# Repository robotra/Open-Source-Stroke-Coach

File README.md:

# Open-Source-Stroke-Coach
This project aims to replicate some of the funcationality of the NK StrokeCoach, but at a much lower cost. 

Current hardware requirement: 
* ESP32 DOIT dev kit
* mpu6050 accelerometer
* I2C display

## Software
Stroke detection is based on the values from the accelerometer, smoothed by a low pass filter. This filtered data is then used to feed a peak detection algorithm, and time between peaks is used to calculate stroke rate. 

## To-do
* GPS
* Save to SD card as GPX file
* Then build out integration to the Strava API
* BLE HRM connection
* UI
* Minimize scope creep
* PCB

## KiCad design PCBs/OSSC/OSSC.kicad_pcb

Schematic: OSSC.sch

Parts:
C1, C3, C5: 0.1uF; C_0402_1005Metric
C2: 2.2nF; C_0402_1005Metric
C4: 2.3nF; C_0402_1005Metric
J1: Conn_01x02_Female; JST_SH_SM02B-SRSS-TB_1x02-1MP_P1.00mm_Horizontal
J2: Conn_01x04; PinHeader_1x04_P1.27mm_Vertical
J3, J4: Conn_01x01; PinHeader_1x01_P1.00mm_Vertical
R1: 10k; R_0603_1608Metric_Pad1.05x0.95mm_HandSolder
R2, R3: 10k; R_0402_1005Metric
U1: MCP1700-3302E_SOT23; SOT-23
U2: ESP32-WROOM-32
U3: MPU-6050; InvenSense_QFN-24_4x4mm_P0.5mm

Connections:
+BATT: J1.2, U1.3 (VI)
GND: C1.1, C3.2, C4.2, C5.1, J1.1, J2.2, U1.1 (GND), U2.1 (GND), U2.15 (GND), U2.38 (GND), U2.39 (GND), U3.1 (CLKIN), U3.9 (AD0), U3.11 (FSYNC), U3.18 (GND)
I2C-SCL: J2.3, R3.2, U2.36 (IO22), U3.23 (SCL)
I2C-SDA: J2.4, R2.2, U2.33 (IO21), U3.24 (SDA)
MPU-6050-INT: U2.23 (IO15), U3.12 (INT)
unnamed: C1.2, R1.1, U2.3 (EN)
unnamed: C2.1, U3.8 (VDDIO)
unnamed: C4.1, U3.20 (CPOUT)
unnamed: C5.2, U3.10 (REGOUT)
unnamed: J3.1, U2.35 (TXD0/IO1)
unnamed: J4.1, U2.34 (RXD0/IO3)
VCC-3.3V: C2.2, C3.1, J2.1, R1.2, R2.1, R3.1, U1.2 (VO), U2.2 (VDD), U3.13 (VDD)

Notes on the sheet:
I2C-Connector for Display

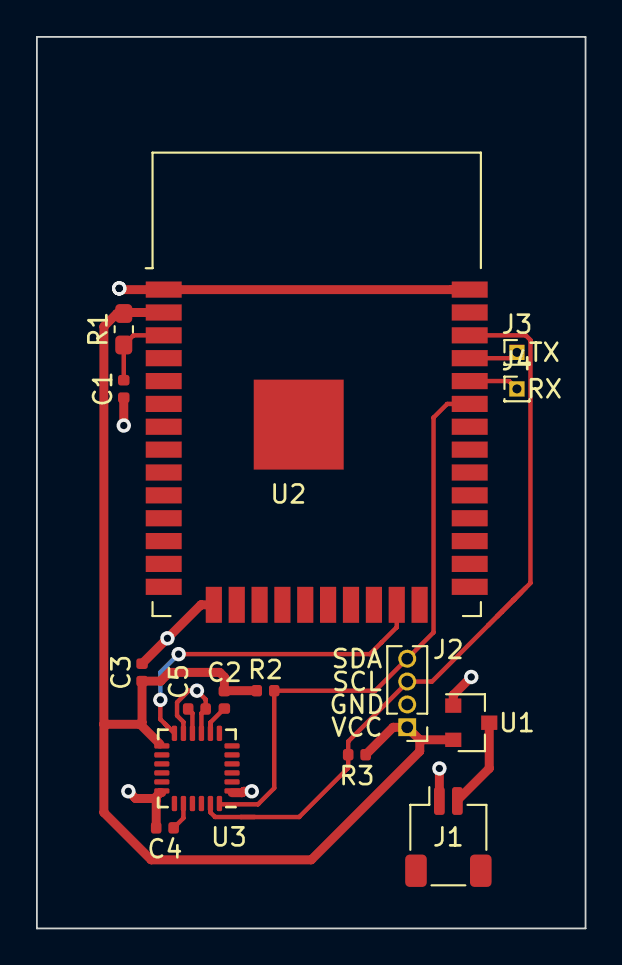
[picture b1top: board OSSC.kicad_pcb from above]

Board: 2 copper layers, 30.5 x 49.5 mm, 15 parts (0 on the bottom side), 12 nets.

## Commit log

2019-08-06 Arduino code
2019-08-14 Serial
    Update for serial output
2019-08-14 gps integration
    disabled interrupts for write to SD
2019-08-14 update to write to sd
2019-08-14 update for calibration values
2019-08-15 Update for file naming
2019-08-16 update to file creation
2019-08-19 Master update
2019-08-20 millis tracking
2019-08-23 Switch to neoGPS
2019-08-24 change to SdFat
2020-05-27 esp32 read data from accelerometer and write to SD card sketch added
2020-05-28 commit to greate ESP32 based logger in order to get some test accelerometer data in order to genreeate a stroke detection algorithm.
2020-05-28 increase sample rate
2020-05-28 add dummy data file
2020-05-29 Redefining things for ESP32
2020-05-29 cleaning up folder
2020-05-29 test
2020-05-29 Test commit from vscode
2020-05-29 Updates to comments
2020-05-29 modifications for detatching interrupt during write to SD in order to hopefully improve logging
2020-05-29 Test commit
2020-05-29 VSCODE
2020-05-29 Updates and placement of missing semicolons
2020-05-29 set sample rate to 100Hz
2020-05-29 Created sketch with no GPS because it really isnt necessary.
2020-05-30 Addition of low pass filter to -nogps test code. Seems to be promising.
2020-06-02 pcb + oled
2020-06-02 create strokeMeasuring code
2020-06-02 added erg handle dummy data that was collected after the LPF
2020-06-03 addition of data captured from a rowing in the 1x
2020-06-03 save a graph of data collected
2020-06-03 addition of circular buffers and real time ish calculation of stroke rate.
2020-06-03 addition of OLED display code
2020-06-03 re-added logging capabilities
2020-06-04 Add files via upload
    NEW KICAD PCB-Layout
2020-06-04 Schematic Change
    -Removed 2 Cap between IC-Ground to Ground
    -Added Power-Up Delay-Circuit for ESP
    -Added Filter-Cap for MPU
2020-06-05 add photo of demo hardware
2020-06-05 Added Components
    Added Components for MPU-6050
    Added I2C-Connector for Display
    Added two Pins for Programming
2020-06-05 updated photo of demo hardware
2020-06-10 creation of PlatformIO related files
2020-06-21 platformIO
2020-06-21 cleaning
2020-09-17 Update to folder organization and renaming of files
2020-09-17 add file with no logging or HR features
2020-09-17 add master file
2020-09-17 modified ignore
2020-09-17 update of time displat, added zeros in single digit seconds
2020-09-18 added sleep if idle
2020-09-21 Addition of sleep timer using LPF
2020-09-25 added some power control and worked on enclosure for the device.
2020-09-28 update of cad files
